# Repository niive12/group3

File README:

#Group 3 Project Folder

for reference:
use IEEE.NUMERIC_STD.ALL;
![conversion 
chart] 
(https://github.com/niive12/group3/blob/master/emb/vhdl-type-conversions.png 
"vhdl conversion")

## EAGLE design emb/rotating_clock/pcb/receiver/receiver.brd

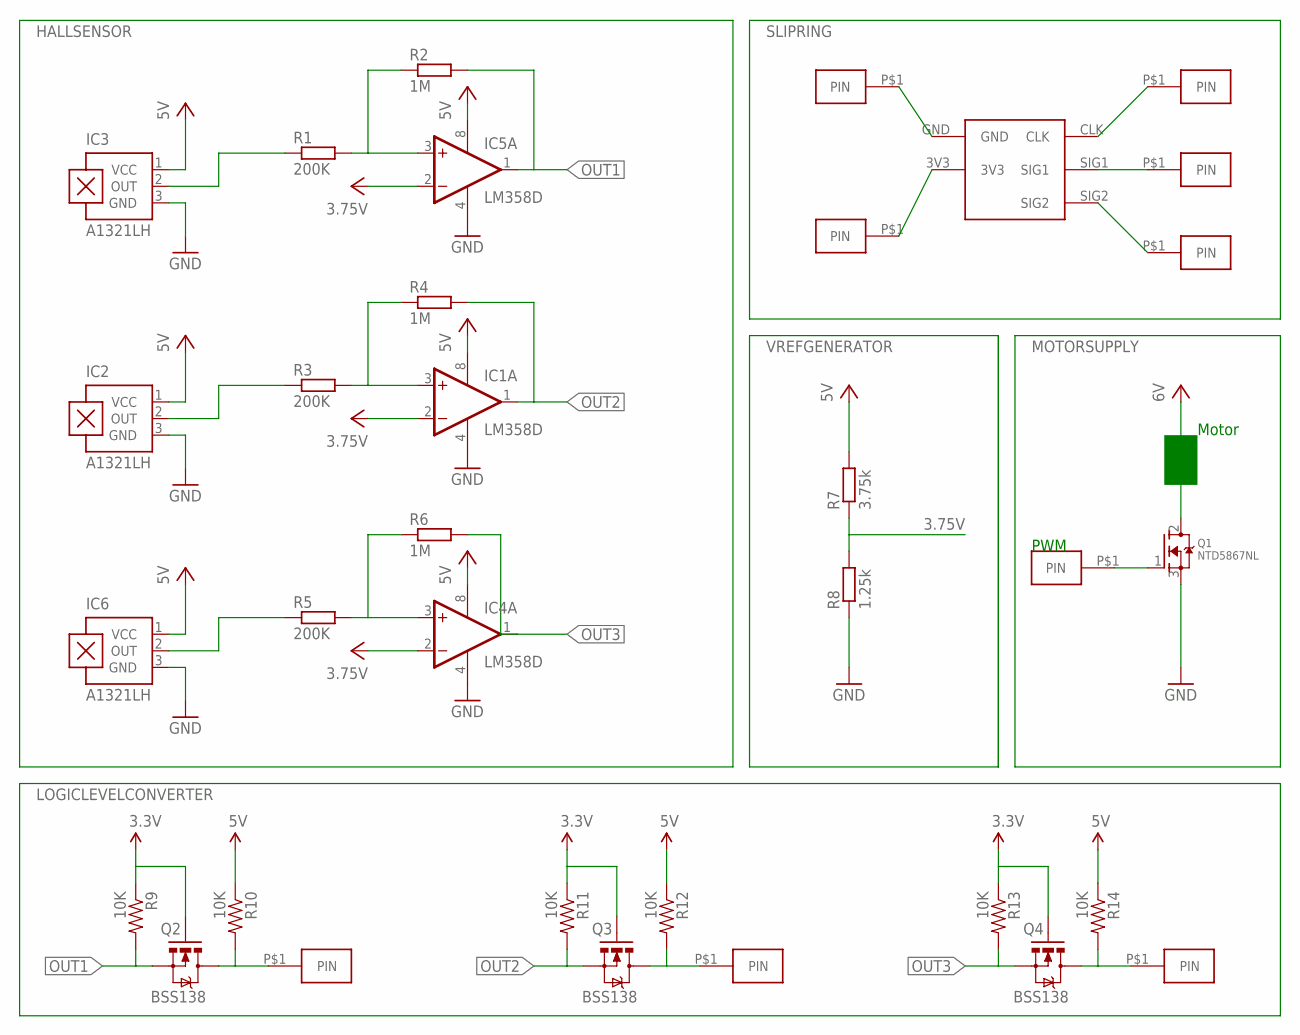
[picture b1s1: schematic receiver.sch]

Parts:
IC1, IC4, IC5: LM358D; SO08
IC2, IC3, IC6: A1321LH; SOT23-W
PWM: PWM; CONNECTOR
Q1: NTD5867NL; TO220V
Q2, Q3, Q4: BSS138; SOT23-3
R1, R3, R5: 200K; R0805
R2, R4, R6: 1M; R0805
R7: 3.75k; R0805
R8: 1.25k; R0805
R9, R10, R11, R12, R13, R14: 10K; 0603-RES
U$1: SLIP-RING
U$2, U$3, U$4, U$5, U$6, U$7, U$8, U$9: CONNECTOR

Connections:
1: IC5.1 (OUT), R2.2
2: IC1.1 (OUT), R4.2
3: IC4.1 (OUT), R6.2
3.75V: IC5.2 (-IN), R7.1, R8.2
5V: IC1.8 (V+), IC2.1 (VCC), IC3.1 (VCC), IC4.8 (V+), IC5.8 (V+), IC6.1 (VCC), R7.2
GND: IC1.4 (V-), IC2.3 (GND), IC3.3 (GND), IC4.4 (V-), IC5.4 (V-), IC6.3 (GND), Q1.3 (S), R8.1
HV: R10.1, R12.1, R14.1
HV1: Q2.3 (D), R10.2, U$4.P$1
HV2: Q3.3 (D), R12.2, U$2.P$1
HV3: Q4.3 (D), R14.2, U$3.P$1
unnamed: IC2.2 (OUT), R3.1
unnamed: IC3.2 (OUT), R1.1
unnamed: IC5.3 (+IN), R1.2, R2.1
unnamed: IC6.2 (OUT), R5.1
unnamed: IC4.3 (+IN), R5.2, R6.1
unnamed: U$1.CLK, U$5.P$1
unnamed: U$1.SIG1, U$6.P$1
unnamed: U$1.SIG2, U$7.P$1
unnamed: U$1.GND, U$8.P$1
unnamed: U$1.3V3, U$9.P$1
OUT1: Q2.2 (S), R9.2
OUT2: Q3.2 (S), R11.2
OUT3: Q4.2 (S), R13.2
R20: IC1.3 (+IN), R3.2, R4.1
VCC: IC1.2 (-IN), IC4.2 (-IN), Q1.2 (D), Q2.1 (G), Q3.1 (G), Q4.1 (G), R9.1, R11.1, R13.1

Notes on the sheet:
Motor
PWM

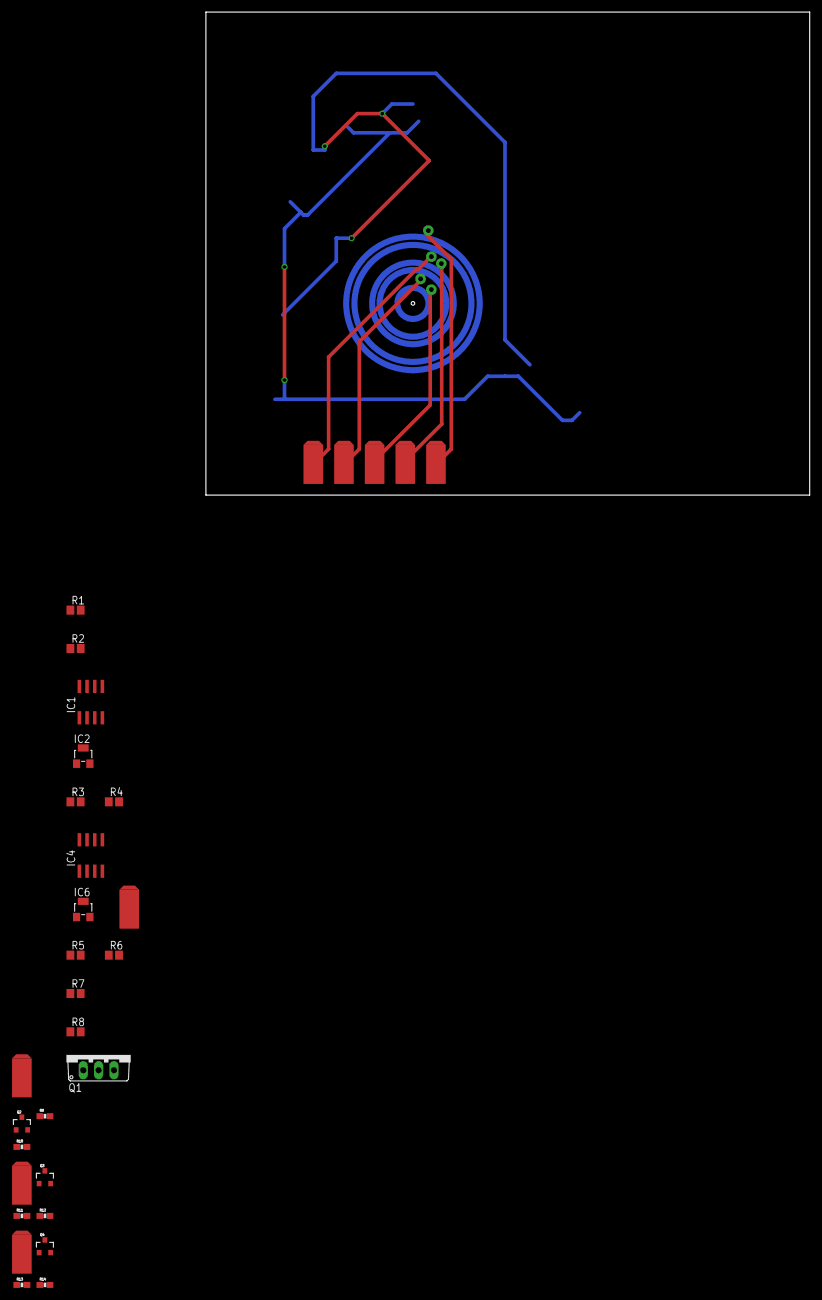
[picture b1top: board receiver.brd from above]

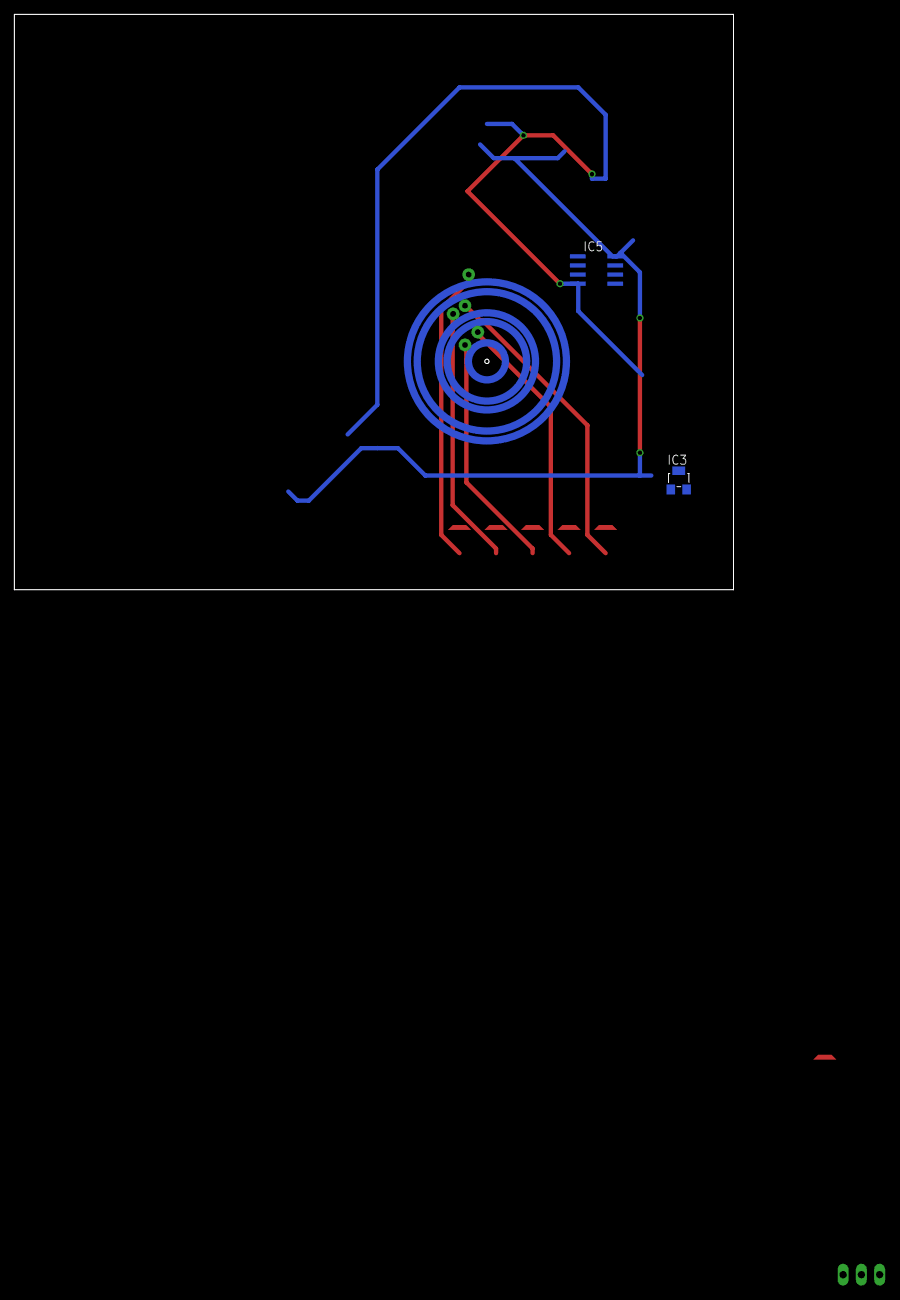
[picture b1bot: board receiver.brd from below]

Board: 2 copper layers, 100.0 x 80.0 mm, 34 parts (2 on the bottom side), 25 nets.

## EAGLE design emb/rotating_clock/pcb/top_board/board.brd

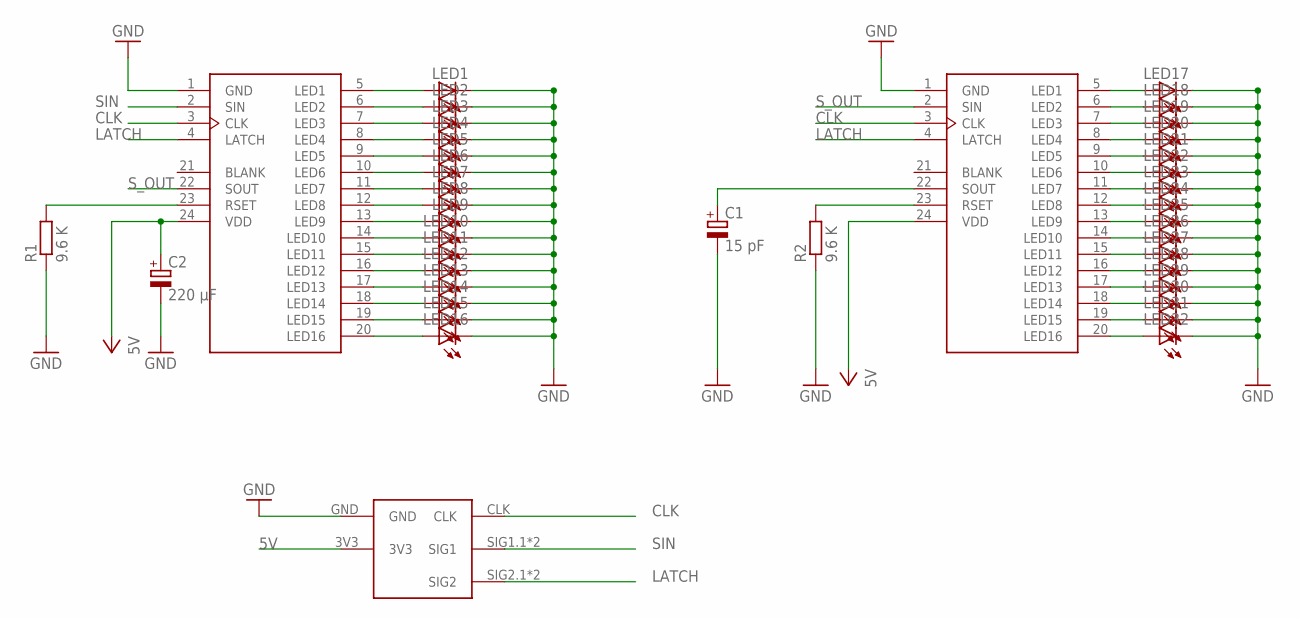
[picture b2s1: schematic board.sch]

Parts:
C1: 15 pF; E5-8,5
C2: 220 µF; E5-8,5
IC1, IC2: CAT4016; SOIC24W
LED1, LED2, LED3, LED4, LED5, LED6, LED7, LED8, LED9, LED10, LED11, LED12, LED13, LED14, LED15, LED16, LED17, LED18, LED19, LED20, LED21, LED22, LED23, LED24, LED25, LED26, LED27, LED28, LED29, LED30, LED31, LED32: LEDCHIPLED-0603-TTW; CHIPLED-0603-TTW
R1, R2: 9.6 K; 0207/10
U$1: SLIP-RING-INVERSE

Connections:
5V: C2.+, IC1.24 (VDD), IC2.24 (VDD), U$1.3V3
C1: C1.+, IC2.22 (SOUT)
CLK: IC1.3 (CLK), IC2.3 (CLK), U$1.CLK
LATCH: IC1.4 (LATCH), IC2.4 (LATCH), U$1.SIG2.1 (SIG2), U$1.SIG2.2 (SIG2)
unnamed: IC1.23 (RSET), R1.2
unnamed: IC2.23 (RSET), R2.2
unnamed: IC2.20 (LED16), LED32.A@1 (A)
unnamed: IC2.19 (LED15), LED31.A@1 (A)
unnamed: IC2.18 (LED14), LED30.A@1 (A)
unnamed: IC2.17 (LED13), LED29.A@1 (A)
unnamed: IC2.16 (LED12), LED28.A@1 (A)
unnamed: IC2.15 (LED11), LED27.A@1 (A)
unnamed: IC2.14 (LED10), LED26.A@1 (A)
unnamed: IC2.13 (LED9), LED25.A@1 (A)
unnamed: IC2.5 (LED1), LED17.A@1 (A)
unnamed: IC2.6 (LED2), LED18.A@1 (A)
unnamed: IC2.7 (LED3), LED19.A@1 (A)
unnamed: IC2.8 (LED4), LED20.A@1 (A)
unnamed: IC2.9 (LED5), LED21.A@1 (A)
unnamed: IC2.10 (LED6), LED22.A@1 (A)
unnamed: IC2.11 (LED7), LED23.A@1 (A)
unnamed: IC2.12 (LED8), LED24.A@1 (A)
unnamed: IC1.5 (LED1), LED1.A@1 (A)
unnamed: IC1.6 (LED2), LED2.A@1 (A)
unnamed: IC1.7 (LED3), LED3.A@1 (A)
unnamed: IC1.8 (LED4), LED4.A@1 (A)
unnamed: IC1.9 (LED5), LED5.A@1 (A)
unnamed: IC1.10 (LED6), LED6.A@1 (A)
unnamed: IC1.11 (LED7), LED7.A@1 (A)
unnamed: IC1.12 (LED8), LED8.A@1 (A)
unnamed: IC1.13 (LED9), LED9.A@1 (A)
unnamed: IC1.14 (LED10), LED10.A@1 (A)
unnamed: IC1.15 (LED11), LED11.A@1 (A)
unnamed: IC1.16 (LED12), LED12.A@1 (A)
unnamed: IC1.17 (LED13), LED13.A@1 (A)
unnamed: IC1.18 (LED14), LED14.A@1 (A)
unnamed: IC1.19 (LED15), LED15.A@1 (A)
unnamed: IC1.20 (LED16), LED16.A@1 (A)
unnamed: C1.-, C2.-, IC1.1 (GND), IC2.1 (GND), LED1.C@1 (C), LED2.C@1 (C), LED3.C@1 (C), LED4.C@1 (C), LED5.C@1 (C), LED6.C@1 (C), LED7.C@1 (C), LED8.C@1 (C), LED9.C@1 (C), LED10.C@1 (C), LED11.C@1 (C), LED12.C@1 (C), LED13.C@1 (C), LED14.C@1 (C), LED15.C@1 (C), LED16.C@1 (C), LED17.C@1 (C), LED18.C@1 (C), LED19.C@1 (C), LED20.C@1 (C), LED21.C@1 (C), LED22.C@1 (C), LED23.C@1 (C), LED24.C@1 (C), LED25.C@1 (C), LED26.C@1 (C), LED27.C@1 (C), LED28.C@1 (C), LED29.C@1 (C), LED30.C@1 (C), LED31.C@1 (C), LED32.C@1 (C), R1.1, R2.1, U$1.GND
SIN: IC1.2 (SIN), U$1.SIG1.1 (SIG1), U$1.SIG1.2 (SIG1)
S_OUT: IC1.22 (SOUT), IC2.2 (SIN)

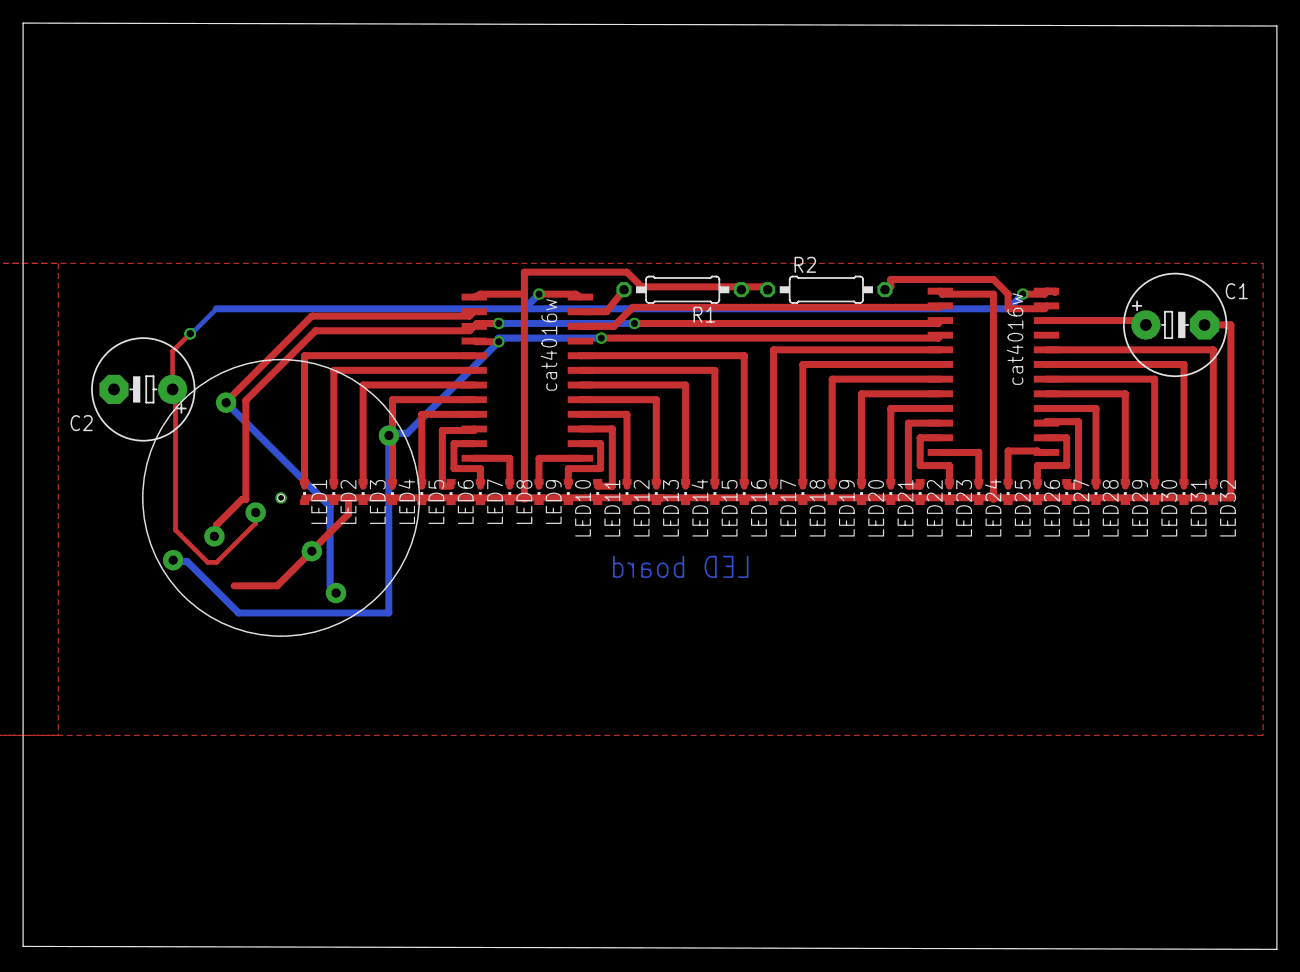
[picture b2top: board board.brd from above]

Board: 2 copper layers, 108.6 x 80.3 mm, 39 parts (0 on the bottom side), 41 nets.

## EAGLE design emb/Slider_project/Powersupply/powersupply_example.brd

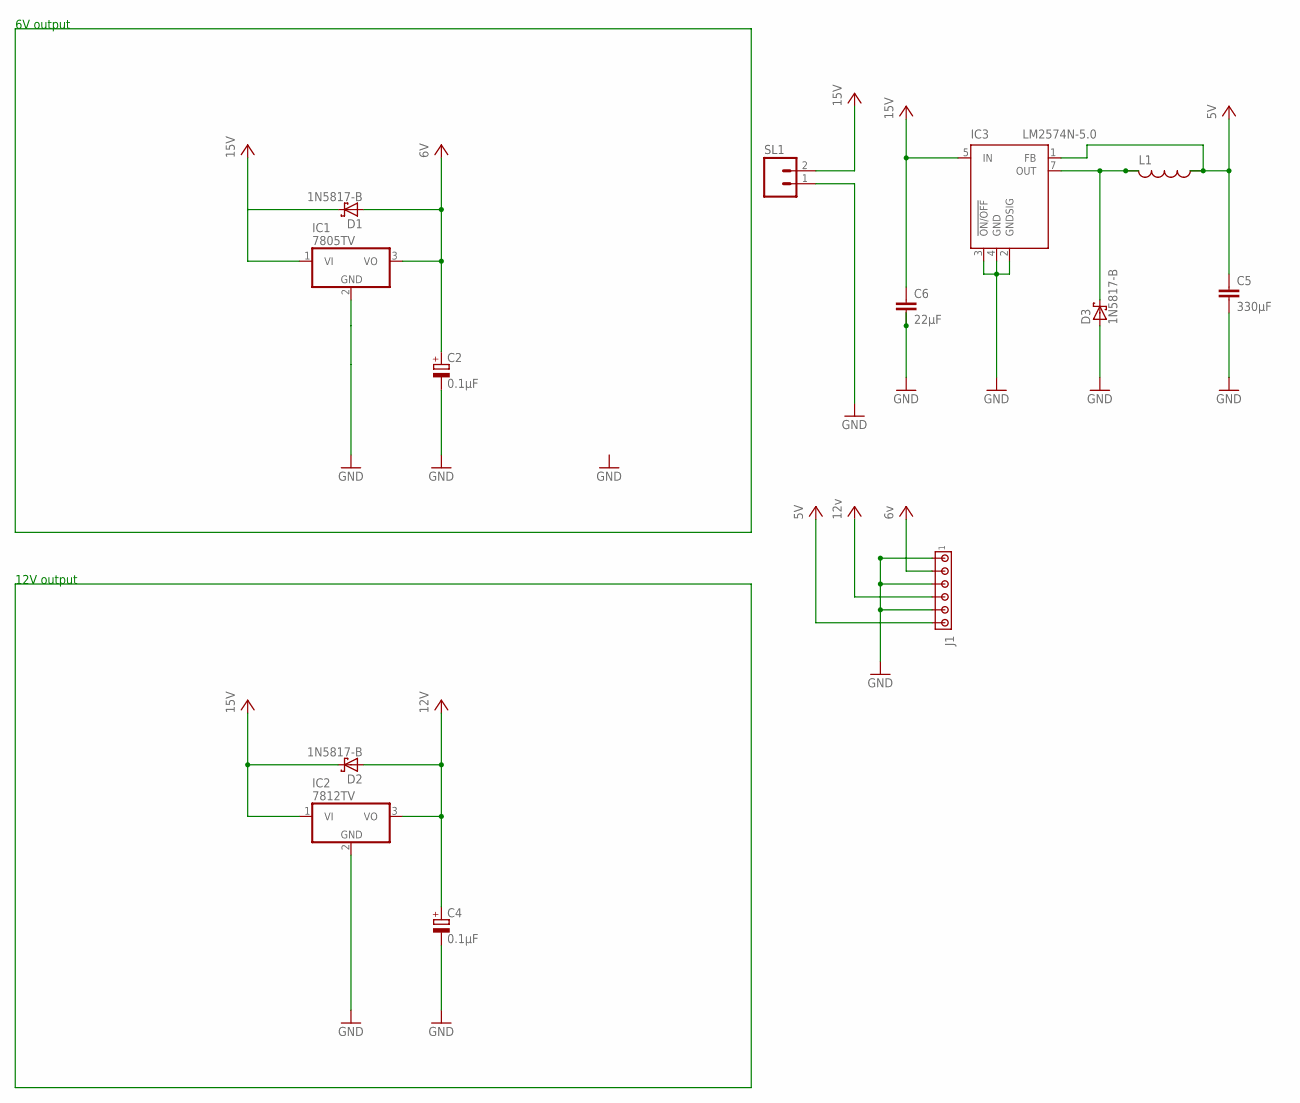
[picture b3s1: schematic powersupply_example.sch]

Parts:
C2, C4: 0.1µF; E2,5-5
C5: 330µF; C025-040X050
C6: 22µF; C025-040X050
D1, D2, D3: 1N5817-B; DO41-7.6
IC1: 7805TV; TO220V
IC2: 7812TV; TO220V
IC3: LM2574N-5.0; DIL08
J1: MTA06-100; 10X06MTA
L1: L-US0204/7; 0204/7
SL1: M02; 02P

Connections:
5V: C5.1, IC3.1 (FB), J1.6, L1.1
6V: C2.+, D1.A, IC1.3 (VO), J1.2
12V: C4.+, D2.A, IC2.3 (VO), J1.4
15V: C6.1, D1.C, D2.C, IC1.1 (VI), IC2.1 (VI), IC3.5 (IN), SL1.2
GND: C2.-, C4.-, C5.2, C6.2, D3.A, IC1.2 (GND), IC2.2 (GND), IC3.2 (GNDSIG), IC3.3 (!ON/OFF), IC3.4 (GND), J1.1, J1.3, J1.5, SL1.1
unnamed: D3.C, IC3.7 (OUT), L1.2

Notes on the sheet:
6V output
12V output

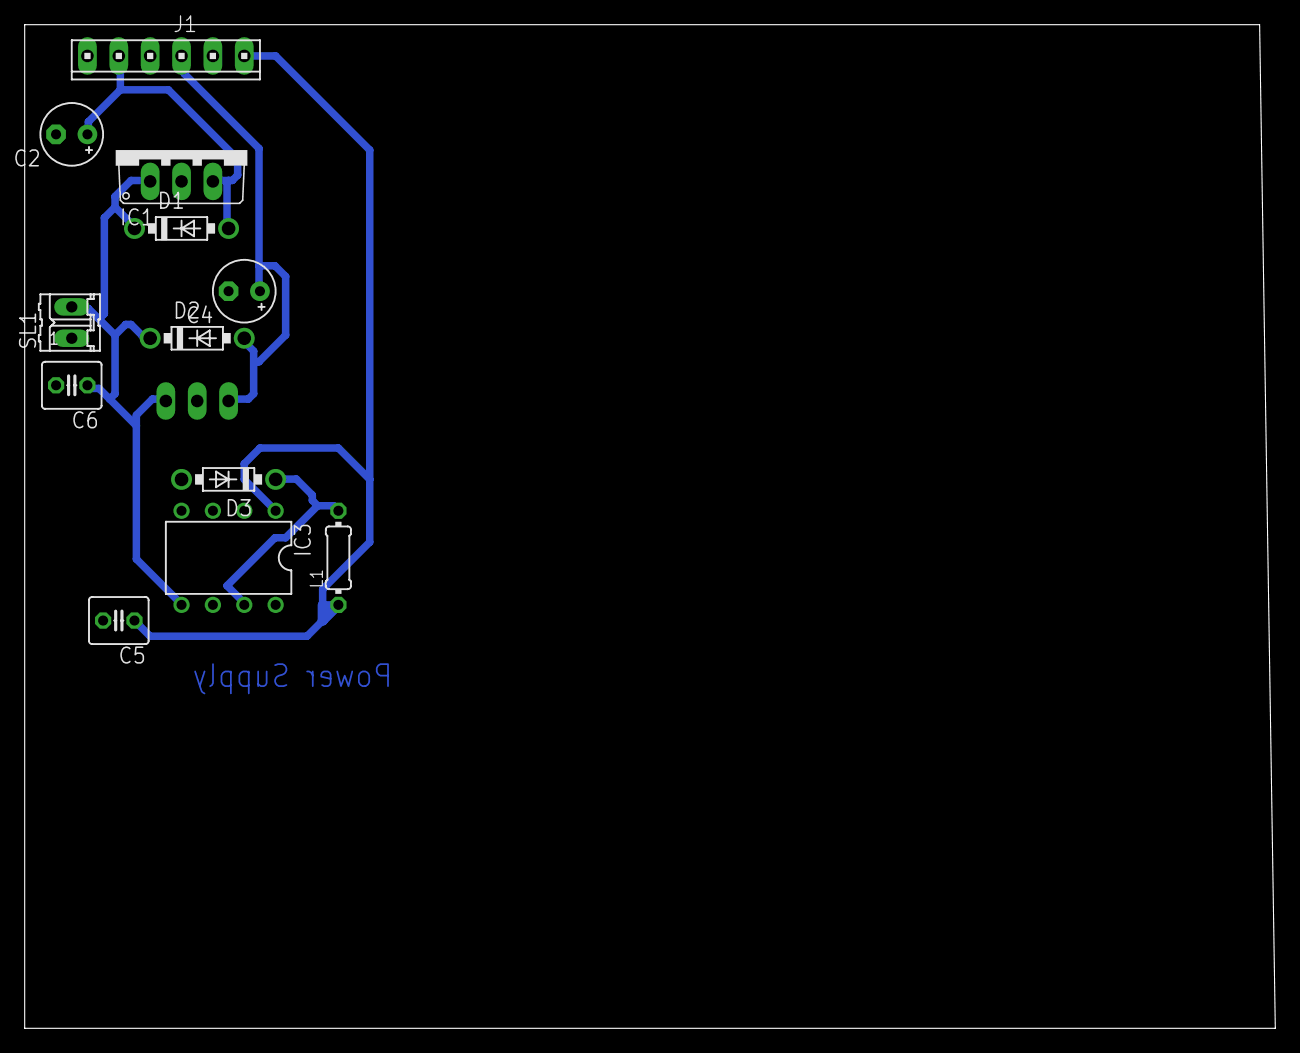
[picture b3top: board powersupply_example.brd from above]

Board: 2 copper layers, 101.3 x 81.3 mm, 13 parts (1 on the bottom side), 6 nets.

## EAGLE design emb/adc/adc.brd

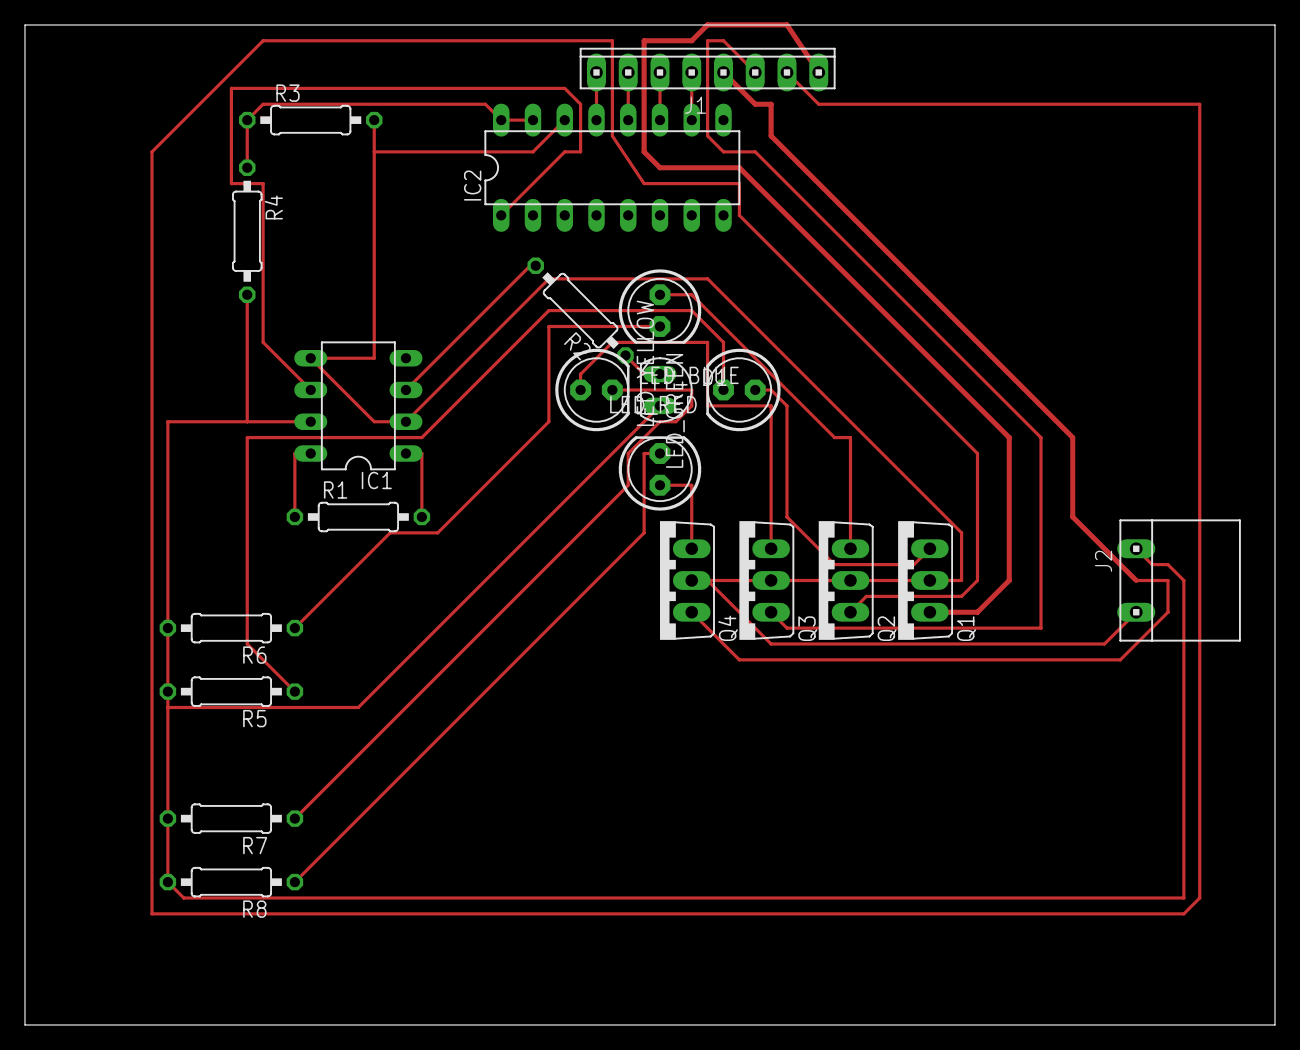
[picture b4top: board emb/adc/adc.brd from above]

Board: 2 copper layers, 100.0 x 80.0 mm, 21 parts (0 on the bottom side), 24 nets.

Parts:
D1: SFH203; SFH205
IC1: AD623N; DIL08
IC2: MCP3008; DIL16
J1: 10X08MTA
J2: 10X03MTA
LED_BLUE: LED5MM
LED_GREEN: LED5MM
LED_RED: LED5MM
LED_YELLOW: LED5MM
Q1, Q2, Q3, Q4: RD06HVF1
R1, R2, R3, R4, R5, R6, R7, R8: 0207/10

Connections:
0V: IC1.2, IC1.5, IC2.14, J2.1, Q1.2, Q2.2, Q3.2, Q4.2, R3.2
12V: D1.A, IC1.7, J2.3, R4.2, R5.2, R6.2, R7.2, R8.2
CLK: IC2.13, J1.8
CS: IC2.10, J1.5
L_B: J1.3, Q3.1
L_G: J1.2, Q2.1
L_R: J1.1, Q1.1
L_Y: J1.4, Q4.1
MISO: IC2.12, J1.7
MOSI: IC2.11, J1.6
unnamed: IC1.1, R1.2
unnamed: IC1.8, R1.1
unnamed: D1.K, R2.1
unnamed: IC1.3, R2.2
unnamed: IC1.6, IC2.1
unnamed: IC2.15, IC2.16, R3.1, R4.1
unnamed: LED_RED.K, R5.1
unnamed: LED_RED.A, Q1.3
unnamed: LED_GREEN.K, R6.1
unnamed: LED_GREEN.A, Q2.3
unnamed: LED_BLUE.K, R7.1
unnamed: LED_YELLOW.K, R8.1
unnamed: LED_BLUE.A, Q3.3
unnamed: LED_YELLOW.A, Q4.3

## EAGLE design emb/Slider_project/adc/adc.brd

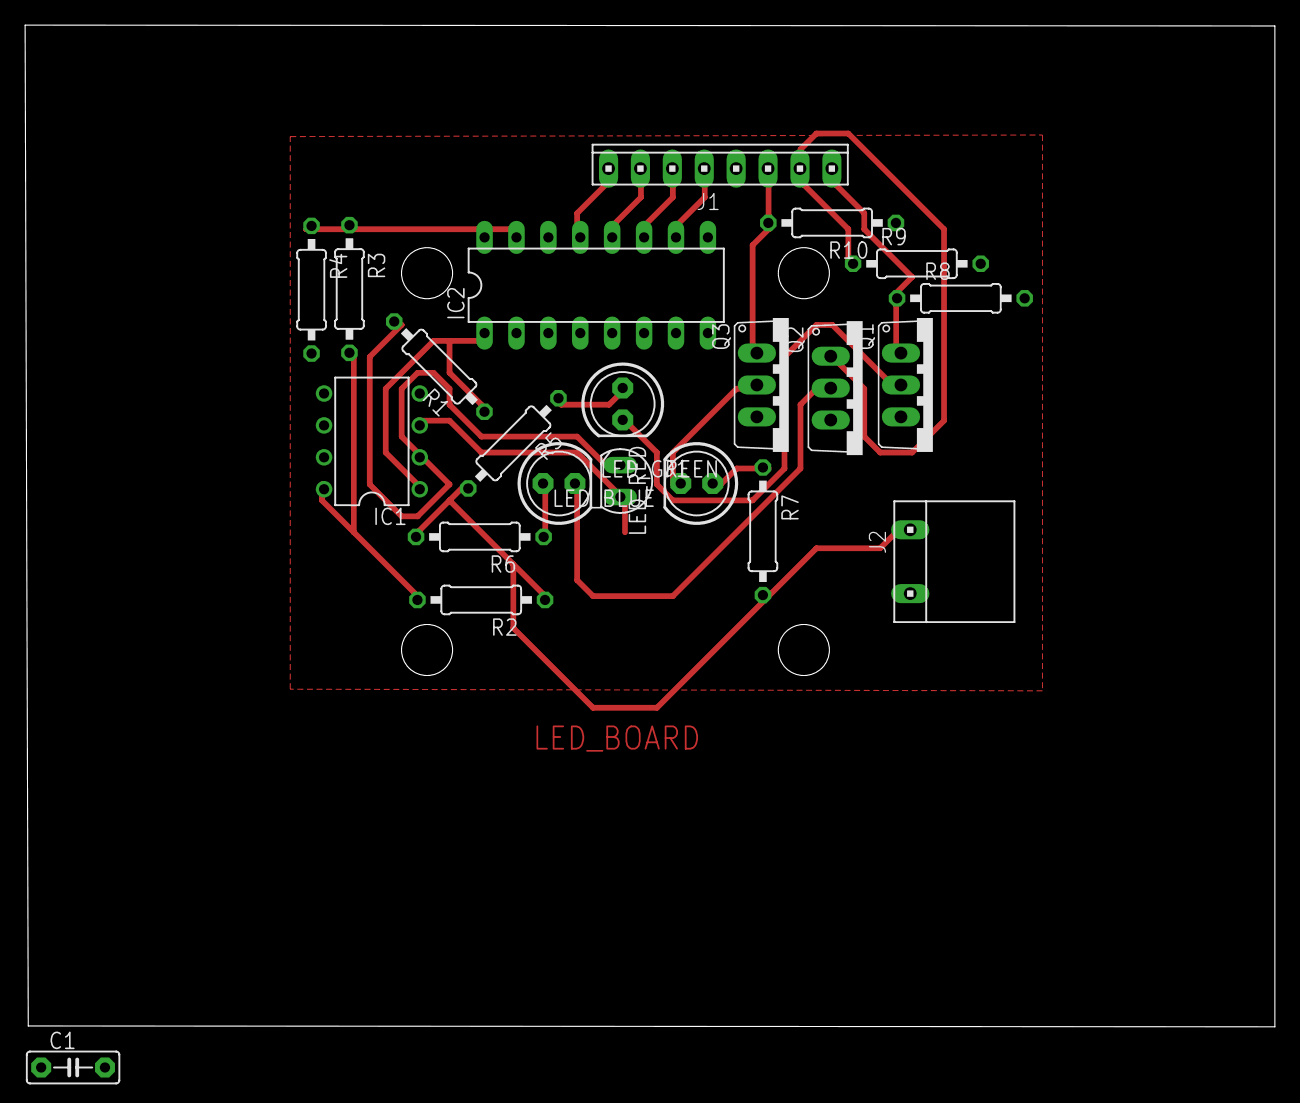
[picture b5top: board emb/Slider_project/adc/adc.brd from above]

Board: 2 copper layers, 99.5 x 79.8 mm, 22 parts (0 on the bottom side), 19 nets.

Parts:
C1: 10 pf; C5B2.5
D1: SFH203; SFH205
IC1: LM2904; DIL08
IC2: MCP3008; DIL16
J1: 10X08MTA
J2: 10X03MTA
LED_BLUE: LED5MM
LED_GREEN: LED5MM
LED_RED: LED5MM
Q1, Q2, Q3: NTD5867NL; TO220V
R1: 100K; 0207/10
R2: 7.5K; 0207/10
R3: 1.2K; 0207/10
R4: 3.3K; 0207/10
R5: 200; 0207/10
R6, R7: 160; 0207/10
R8, R9, R10: 12K; 0207/10

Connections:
0V: D1.A, IC1.3, IC1.4, IC2.9, IC2.14, J2.1, Q1.3, Q2.3, Q3.3, R4.2, R8.2, R9.2, R10.1
3.3V: IC2.15, IC2.16, R3.1, R4.1
4.5V: IC1.8, R2.2, R3.2
12V: J2.3, R2.1, R5.2, R6.2, R7.2
CLK: IC2.13, J1.8
CS: IC2.10, J1.5
L_B: J1.3, Q3.1, R10.2
L_G: J1.2, Q2.1, R9.1
L_R: J1.1, Q1.1, R8.1
MISO: IC2.12, J1.7
MOSI: IC2.11, J1.6
unnamed: C1.1, D1.K, IC1.2, R1.2
unnamed: LED_BLUE.K, Q3.2
unnamed: LED_RED.A, R5.1
unnamed: LED_RED.K, Q1.2
unnamed: C1.2, IC1.1, IC2.1, R1.1
unnamed: LED_BLUE.A, R7.1
unnamed: LED_GREEN.A, R6.1
unnamed: LED_GREEN.K, Q2.2

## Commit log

2015-09-14 Nikolaj has access
2015-09-14 linux driver guide
2015-09-14 lego program added
2015-09-15 added some vhdl source
2015-09-16 state machine works
2015-09-16 added files
2015-09-17 added files, doesn't work
2015-09-17 Matthias has access
2015-09-17 got it working
2015-09-17 double and long press works
2015-09-17 Added testbench for fsm
2015-09-17 state machine drawn in tikz
2015-09-21 made crude PID line follow
2015-09-21 python script to find lego device
2015-09-21 turning functions tested
2015-09-24 images
2015-09-24 adding state_machine simulation
2015-09-24 added comments
2015-09-24 split the testbenches up
2015-09-28 sokoban code
2015-09-28 test code
2015-09-28 I don't know why it is not working
2015-09-30 it works on small example, will crash on 35M nodes
2015-10-01 block-diagram simple
2015-10-01 block diragram
2015-10-01 Powersupply PCB
2015-10-02 Updated PCB board
2015-10-05 added mapping, a solution is found
2015-10-06 SPI communication sending packages running
2015-10-07 Communication both directions + updated power supply board
2015-10-07 solution is found, reduced memory to 500mb
2015-10-08 wrong file
2015-10-08 Real powersupply
2015-10-08 renamed
2015-10-11 initial thoughts on the robot construction problems
2015-10-18 Added notes to report + added moveset table
2015-10-18 cleaned up the text
2015-10-18 added author
2015-10-19 added picture and made it IEEE style
2015-10-22 powersupply board updated
2015-10-22 Added sources and simulations for LED driver and Servo
2015-10-22 Added Toplevel module and simulation skeleton for slide
2015-10-24 first test, adc
2015-10-25 Report VHDL modules described
2015-10-26 Added test section + modified Circuits
2015-10-27 Added details to power supply
2015-10-27 new board
2015-10-27 adc files updated
2015-10-27 rettelser til power supply
2015-10-27 circuits.tex rettet
2015-10-27 Adding datasheet
2015-10-27 added datasheets
2015-10-27 merge
2015-10-27 started the description of LEDs
2015-10-27 small section about the photo diode added
2015-10-27 small changes
2015-10-28 Added changes to report
2015-10-28 Adding intro
2015-10-28 Added sources to project
2015-10-28 updated figures
2015-10-28 my fix for spi
2015-10-28 prolonged CS pulse
2015-10-28 added include
2015-10-28 added important conversion file
2015-10-28 It works
2015-10-28 made a graph... it is not as pretty as I have hoped...
2015-10-29 added plots of ADC communication
2015-10-29 Added sources
2015-10-29 moved to a subsection
2015-10-29 rewrote to KNN
2015-10-29 Adding serial communication C++
2015-10-30 Added pictures from test
2015-10-30 test section
2015-10-30 Added some stuff to report
2015-10-30 included figure of the adc board
2015-10-30 changed a bit here and there
2015-10-31 changes made to the report
2015-11-01 I AM SO SO SO SORRY commit
2015-11-01 eagle files
2015-11-01 added image
2015-11-01 merge1
2015-11-01 special considerations updated, added an updated figure
2015-11-01 added picture
2015-11-01 Added citations
2015-11-01 power supply test added
2015-11-01 referece
2015-11-01 Changed some stuff in report
2015-11-01 EVERYTHING IS AWESOME
2015-11-01 everything works when you are part of utosnet
2015-11-01 Serial Code working
2015-11-01 Made folder for zip
2015-11-01 conclusion
2015-11-01 analog analysis
2015-11-01 adc communication
2015-11-01 missing figure?
2015-11-01 Added changes to tosnet section
2015-11-01 added demonstration video
2015-11-02 meeting ajourned
2015-11-03 code is working, and I know the path length
2015-11-03 Tuned Turnparameters
2015-11-05 Made more structure in the folder
2015-11-05 Cleanup of folders
2015-11-05 orderlist updated
2015-11-09 project overview
2015-11-09 led board schematic added
2015-11-09 figure to illustrate the slipring
2015-11-11 Added compass function
2015-11-12 initialized board
2015-11-16 Modified main with compass
2015-11-16 fixed memory leak
2015-11-16 print result as a C initializer
2015-11-16 fixed error manually in file, will fix in code later. The spec_result.h can be used for testing
2015-11-18 added detector so escapeless walls are detected
2015-11-19 Finalized main.nxc for AI
2015-11-19 Created files for clock
2015-11-20 updated dead_lock detector
2015-11-23 optimized informed
2015-11-23 updated solution so it is for the 2015 map
2015-11-23 added 2015 map
2015-11-23 headers
2015-11-23 updated C string
2015-11-23 added special cost
2015-11-23 added right as the preferred turn when turning twice
2015-11-25 spec_result updated
2015-11-25 added results
2015-11-25 Removed unimportant stuff
2015-11-26 Modified car
2015-11-26 led_board updated
2015-11-26 Added PID and updated twi_controller
2015-11-26 clock added
2015-11-29 Created report structure
2015-11-29 updated competition map
2015-11-29 Changed PID
2015-11-29 update sensor function
2015-11-29 rotate by difference
2015-11-29 Added robot.tex
2015-11-29 tab correction
2015-11-29 Modified robot.tex
2015-11-29 left turn image
2015-11-30 notes to the turn
2015-11-30 line following figure
2015-12-03 shaft
2015-12-03 shaft updated
2015-12-03 Added datasheet motor
2015-12-03 Added caseing model
2015-12-03 added datasheet
2015-12-04 moved introduction
2015-12-04 sokoban description added
2015-12-04 added images and bibtex
2015-12-04 added some percentages to show how effecient the improvements are
2015-12-06 Report stuff
2015-12-06 Update robot section
2015-12-06 Update robot section again
2015-12-07 robot optimal stuff
2015-12-07 Added picture of robot
2015-12-07 added figures
2015-12-07 small refrasing changes
2015-12-08 sokoban solver works now with optimal path
2015-12-08 added robot movement section
2015-12-08 Schematic and pcb design
2015-12-10 updated shaft to have interlocking design
2015-12-10 slip ring eagle library
2015-12-10 added slip ring board
2015-12-10 Corrected Report
2015-12-11 Added test section
2015-12-11 complexity
2015-12-11 memory size
2015-12-11 wrapfigures
2015-12-11 added timing for the optimized thing
2015-12-11 final version
2015-12-18 Added report stuff
2015-12-18 Inital led communication
2015-12-18 ring connector and clock controller described
2015-12-18 label
2015-12-18 Added bottom board schematic
2015-12-18 Added reference to some datasheets
2015-12-18 test description
2015-12-18 made bot board smaller
2015-12-19 Added housing png
2015-12-19 Added construction-tex
2015-12-19 Updated board
2015-12-19 display_controller
2015-12-20 shaft image added
2015-12-20 top level
2015-12-20 Random commit
2015-12-20 Updated bot board schematic
2015-12-20 fixed the vdhl
2015-12-21 waveform
2015-12-21 Creating files
2015-12-21 updated intro
2015-12-21 Reportstuff
2015-12-21 clock control
2015-12-21 Added llc part
2015-12-21 added top board again
2015-12-21 Added to discussion
2015-12-21 updated git ignore
2015-12-21 construction described
2015-12-21 Skrald
2016-01-20 Adding missing files
2016-02-29 readme
